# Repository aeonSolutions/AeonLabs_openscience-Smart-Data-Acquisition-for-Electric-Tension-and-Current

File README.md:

[PCB-Prototyping-Catalogue](https://github.com/aeonSolutions/PCB-Prototyping-Catalogue)  >>  [Laboratory Automation](https://github.com/aeonSolutions/PCB-Prototyping-Catalogue/tree/main/Laboratory%20Automation)  >>  Smart Data Acquisition for Electric Tension and Current

<br>

# Smart Data Acquisition for Electric Tension and Current
This is the repository for revision "11-2023" of the 16-bit Smart DAQ Device with a unique data fingerprint able to do experimental data upload to any data repository. This data acquisition device has oboard the INA237 IC and is suited for electric current measurements (amperage) and also electric tension (voltage) from an external power source. This IC from Texas Instruments is an ultra-precise digital power monitor with a 16-bit delta-sigma ADC specifically designed for current-sensing applications with common-mode voltage support from –0.3 V to +85 V. For more detailed information about this IC, see the datasheet [here](https://www.ti.com/product/INA237).

<br>

### Circuit Schematic
The circuit schematic for this smart DAQ can be found on the folder "circuit schematic" [here](https://github.com/aeonSolutions/AeonLabs_openscience-Smart-Data-Acquisition-for-Electric-Tension-and-Current/tree/main/Circuit%20Schematic). 

<br>

### Q & A
If you have a question and looking for an answer, there's a **Discussions** chat on the menu above.  Here's the [link](https://github.com/aeonSolutions/AeonLabs_openscience-Smart-Data-Acquisition-for-Electric-Tension-and-Current/discussions). You can post any question related to any of the Smart Data Acquisition devices and Experimental Setups.

<br>

### Known Experimental Tests
This smart data acquisition devices is compatible for the following laboratory experimental tests:

#### [NT Build 492](http://www.nordtest.info/wp/1999/11/21/concrete-mortar-and-cement-based-repair-materials-chloride-migration-coefficient-from-non-steady-state-migration-experiments-nt-build-492/): Concrete, mortar and cement-based repair materials: Chloride migration coefficient from non-steady-state migration experiments

See [here](https://github.com/aeonSolutions/Open-Scientific-Research/wiki/Rapid-Chloride-Migration-Test-(NT-Build-492)) a description of this experimental test procedure using the NT Build 492. 

<br>
  
#### other tests ...

<br>
<br>
 
## Compatibility

<p align="center">

</p>

<br>

## What one additionally needs
- [USB to UART/USB TTL firmware burner for 5V and 3.3V MCUs ](https://github.com/aeonSolutions/PCB-Prototyping-Catalogue/blob/main/DIY-Maker/README.md)
- [Upgradable ESP32 MCU](https://github.com/aeonSolutions/AeonLabs-Upgradable-MCU-ESP32)

<br />
<br />

**Get a Notification on every PCB update**

|  | You can fill in your [email here (Google form)](https://docs.google.com/forms/d/e/1FAIpQLScErMgQYRdA-umvCjvTPPrCO7Lg1QYowTxb7vfa8cTfrcPEAA/viewform?usp=pp_url) and I'll send a reminder when a new PCB prototype is made available here or a new revision for an existing PCB. Stay tuned! |
|-------------|------|

<br>
<br>

## Author

You can get in touch with me on my LinkedIn Profile:

#### Miguel Tomas

You can also follow my GitHub Profile to stay updated about my latest projects: 

**Hire me**

If you like my work here and are looking to design and deploy your own smart device you can hire me on:

- [Fiverr](https://www.fiverr.com/s/GjmPxe). The price starts at $25
- [Guru](https://www.guru.com/freelancers/miguel-tomas)
  
<br>

### Be supportive of my dedication and work towards technology education and buy me a cup of coffee
The PCB Desgin Files i provide here for anyone to use are free. If you like this Smart Device or use it, please consider buying me a cup of coffee, a slice of pizza or a book to help me study, eat and think new PCB design files.

<br />

### Make a donation on Paypal
Make a donation on paypal and get a TAX refund*.

<br>

### Support all these open hardware projects and become a patreon  
Liked any of my PCB KiCad Designs? Help and Support my open work to all by becomming a LDAD Patreon.
In return I will give a free PCB design in KiCad to all patreon supporters. To learn more go to patreon.com. Link below.

<br />
<br />

______________________________________________________________________________________________________________________________
### License

Before proceeding to download any of AeonLabs software solutions for open-source development and/or PCB hardware electronics development make sure you are choosing the right license for your project. See [AeonLabs Solutions for Open Hardware & Source Development](https://github.com/aeonSolutions/PCB-Prototyping-Catalogue/wiki/AeonLabs-Solutions-for-Open-Hardware-&-Source-Development) for more information.

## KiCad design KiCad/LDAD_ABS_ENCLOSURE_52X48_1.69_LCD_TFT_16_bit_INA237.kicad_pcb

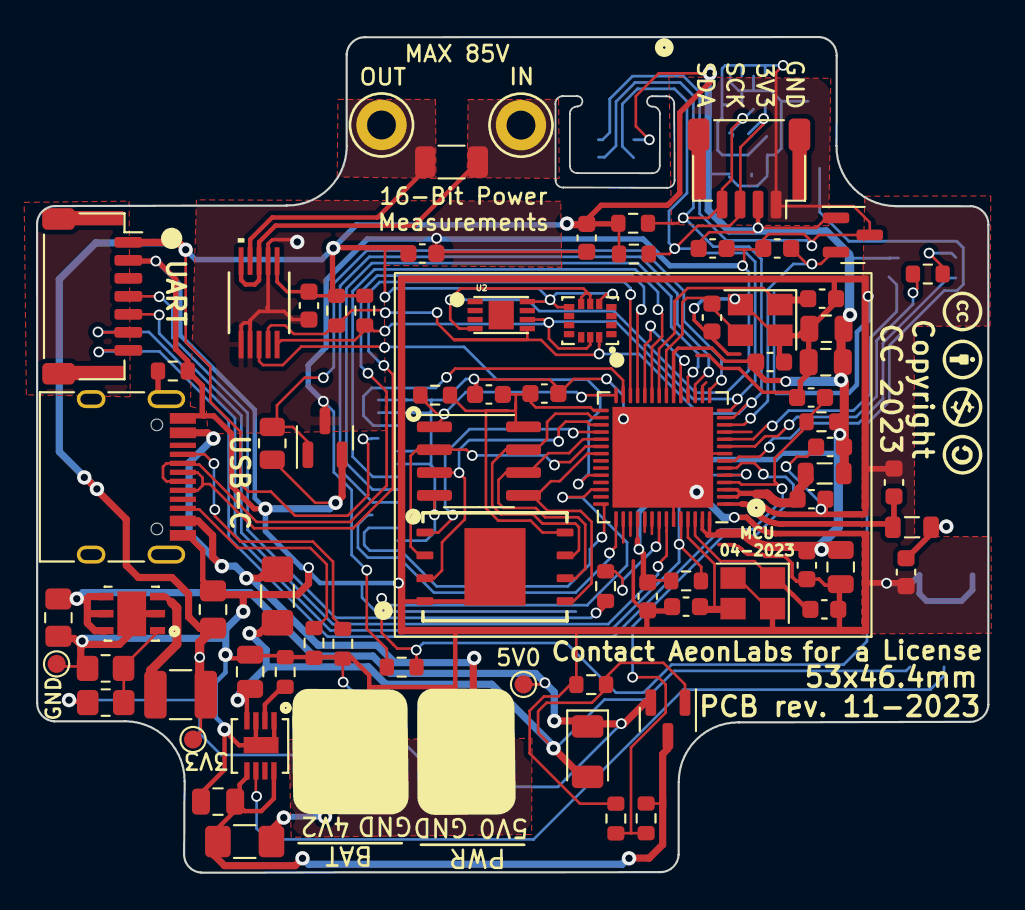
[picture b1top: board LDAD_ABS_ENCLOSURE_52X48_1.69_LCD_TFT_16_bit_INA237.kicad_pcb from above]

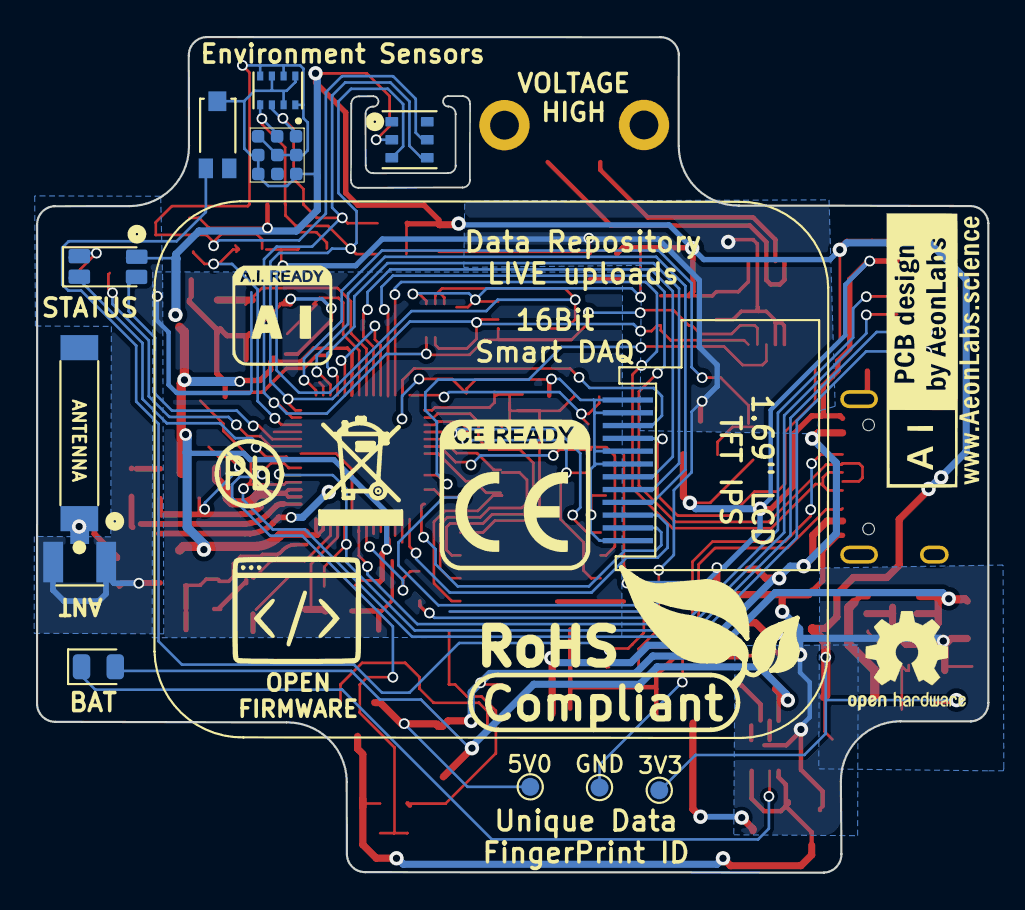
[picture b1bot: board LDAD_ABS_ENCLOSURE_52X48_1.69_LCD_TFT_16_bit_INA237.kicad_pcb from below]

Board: 2 copper layers, 52.9 x 46.4 mm, 90 parts (15 on the bottom side), 57 nets.

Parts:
ATH20_C2: 100nF; C_0603_1608Metric
ATSHA_C1: 100nF; C_0603_1608Metric
AUR1: AUR9718x_DFN_3x3mm_6_pin; AUR9718 ST1S09 SON95P300X300X100-7N
AUR_C1: 22uF; C_0805_2012Metric_Pad1.18x1.45mm_HandSolder
AUR_C2: 4.7uF; C_0805_2012Metric_Pad1.18x1.45mm_HandSolder
AUR_R1: 75k; R_0805_2012Metric_Pad1.20x1.40mm_HandSolder
AUR_R2: 24k; R_0805_2012Metric_Pad1.20x1.40mm_HandSolder
AUR_l1: 3.3uF; L_1210_3225Metric
BAT_FUSE1: Polyfuse; Fuse_1206_3216Metric_Pad1.42x1.75mm_HandSolder
BAT_SENSE_R1, BAT_SENSE_R2: 100k; R_0603_1608Metric
CN3065_C2: 4.7uF; C_0805_2012Metric
CN3065_R1: 1K8; R_0603_1608Metric
CN3065_STDBY_LED1: LED; LED_0805_2012Metric
CN3965_C1: 22uF; C_0805_2012Metric
DMP1045U_1: DMP1045U; SOT-23
DMP1045_R1: 10K; R_0603_1608Metric
DMP1045_SCHOT1: D_Schottky; D_1206_3216Metric
EPS1: ESP32-PSRAM_LY68L6400S; SOIC-8_3.9x4.9mm_P1.27mm
ER1: 1R; R_1206_3216Metric
ESP32S1: ESP32-S3; QFN-56-1EP_7x7mm_P0.4mm_EP5.6x5.6mm
ESP32_SHIELD1: RFShield_OnePiece; ESP32-S3 GND Shield
ESP_FLASH1: W25Q128JVS; WSON8 FLASH SPI SON127P800X600X80-9N
E_DTR_R1: 10k; R_0603_1608Metric
E_LNA_ANT1: AN9520; 2.4ghZ WIFI ANTENNA AN9520_ANT2-SMD-9.5X2.1X1.0MM
E_LNA_ANT2: U.FL-R-SMT(01); RF Antenna IPEX SMD PCB HRS_U.FL-R-SMT(01)
E_LNA_C1, E_LNA_C2: 2.7pF; C_0603_1608Metric
E_LNA_l1: 1.8nH 5%; L_0805_2012Metric
E_RTS_C1: 100nF; C_0603_1608Metric
E_RTS_R1: 10k; R_0603_1608Metric
E_SPI_C1: 1uF 10% 50V; C_0603_1608Metric
E_SPI_C2: 100nF 10% 16V; C_0603_1608Metric
E_UART_TX_1: 499R; R_0603_1608Metric
E_VDDA_C1: 100nF; C_0603_1608Metric
E_VDDA_C2: 1uF 10% 50V; C_0805_2012Metric
E_VDD_3_C1, E_VDD_3_C2: 10uF 20% 6.3V; C_0805_2012Metric
E_VDD_3_C3, E_VDD_3_C4: 100nF 10% 16V; C_0603_1608Metric
E_VDD_CPU_C1: 100nF 10% 16V; C_0603_1608Metric
E_VDD_L1: 12nH 5%; L_0805_2012Metric
E_VDD_RTC_C1: 100nF 10% 16V; C_0603_1608Metric
E_XTAL32_1: 32.768Mhz 22pF+-10PPM; Crystal_SMD_3225-4Pin_3.2x2.5mm
E_XTAL32_C1, E_XTAL32_C2, E_XTAL40_C1, E_XTAL40_C2: 22pF 5% 50V; C_0603_1608Metric
E_XTAL40_1: 40Mhz 22pF+-10PPM; Crystal_SMD_3225-4Pin_3.2x2.5mm
ExtSWBAT_PLUG2: Conn_01x03_Female; JST_SH_SM03B-SRSS-TB_1x03-1MP_P1.00mm_Horizontal
I2C_PLUG1: I2C6; JST_SH_SM04B-SRSS-TB_1x04-1MP_P1.00mm_Horizontal
I2C_SCL_R1, I2C_SDA_R1: 10k; R_0603_1608Metric
IC_ENS1: ENS160 Gas Semsor
IMR1, IMR2: 10K; R_0603_1608Metric
IMU1: LSM6DS3; LSM6DS3 Motion Sensor PQFN50P300X250X86-14N
INA4_C1: 100nF; C_0603_1608Metric
J1: TYPE-C-31-M-12; USB_C_Receptacle_HRO_TYPE-C-31-M-12
JICSP1: Conn_01x07_Socket; JST_SH_SM07B-SRSS-TB_1x07-1MP_P1.00mm_Horizontal
LCD1: Conn_01x12_Male; 1,69 inch LCD IPS TFT
LED1: LED_GBRC; LED_1206_3210_RGB_Metric
LR1: 330R; R_0603_1608Metric
MTRR1: 10k; R_0805_2012Metric
MTRT1: NPN; SOT-23
PSRAM_R1: 100K; R_0603_1608Metric
PWR_FUSE1: Polyfuse; Fuse_1206_3216Metric_Pad1.42x1.75mm_HandSolder
PWR_PLUG1: Screw_Terminal_01x02; JST_SH_SM02B-SRSS-TB_1x02-1MP_P1.00mm_Horizontal
Sign-PbFree: LOGO_PBFREE
Sign-RecycleBin: LOGO_RECYCLEBIN_1
Sign-RoHS: LOGO_ROHS_1
TMPR1: 10K; R_0603_1608Metric
TP1, TP1#2: VIN; TestPoint_Pad_D1.0mm
TP2, TP2#2: VOut; TestPoint_Pad_D1.0mm
TP3, TP3#2: GND; TestPoint_Pad_D1.0mm
U1: MCP1525-TT; SOT-23
U2: ATSHA204A-MAHDA-T; ATSHA204A-MAHDA-T UDFN-8
U3: Battery_charger_CN3065_QFN8; QFN8 3.1x2.9mm QFNn-8 3x3 SON80P400X400X100-9N
U4: AHT20; AHT20 HT Sensor PSON100P300X300X110-6N
U5: INA237AIDGSR; INA237
U6: TEMT6000; TEMT6000-SEN
U7: BMP280; XDCR_BMP280
USB_PLUG_R1, USB_PLUG_R3: 5k1; R_0603_1608Metric
USB_PLYG_R2: 150K; R_0603_1608Metric
VOLTAGE_REF_C1, VOLTAGE_REF_C2: 100nF; C_0603_1608Metric

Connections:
3V3: ATH20_C2.2, ATSHA_C1.2, AUR_C1.1, AUR_R1.1, AUR_l1.1, ESP32S1.20 (VDD3P3_RTC), ESP32S1.46 (VDD3P3_CPU), ESP32S1.55 (VDDA), ESP32S1.56 (VDDA), E_DTR_R1.1, E_RTS_R1.1, E_VDDA_C1.2, E_VDDA_C2.2, E_VDD_3_C1.1, E_VDD_3_C2.1, E_VDD_3_C3.1, E_VDD_CPU_C1.1, E_VDD_L1.1, E_VDD_RTC_C1.1, I2C_PLUG1.2, I2C_SCL_R1.1, I2C_SDA_R1.2, IC_ENS1.4 (VDD), IC_ENS1.5 (VDDIO), IC_ENS1.7 (CS), IMR1.1, IMR2.1, IMU1.5 (VDDIO), IMU1.8 (VDD), INA4_C1.2, JICSP1.1, LCD1.4, LED1.4 (K), TP2.1, TP2#2.1, U1.1 (Vin), U2.8 (VCC), U4.2 (VDD), U5.6 (VS), U6.COLLECTOR, U7.2 (CSB), U7.6 (VDDIO), U7.8 (VDD), VOLTAGE_REF_C1.2
BAT_SENSE_IO21: BAT_SENSE_R1.1, BAT_SENSE_R2.2, ESP32S1.6 (GPIO1/ADC1_CH0)
CHIP_EN: ESP32S1.4 (CHIP_PU/RESET), E_RTS_C1.2, E_RTS_R1.2, JICSP1.7
DAC_CALIBRATION: ESP32S1.19 (GPIO14/ADC2_CH3), ESP32S1.24 (GPIO18/ADC2_CH7/DAC_1)
ESP_GPIO0_BOOT-DTR: ESP32S1.5 (GPIO0/BOOT), ESP32S1.52 (GPIO46), E_DTR_R1.2, JICSP1.6
GND: AUR1.2 (GND), AUR1.7 (GND), AUR_C1.2, AUR_C2.2, AUR_R2.2, BAT_SENSE_R1.2, CN3065_C2.1, CN3065_R1.1, CN3965_C1.1, DMP1045_R1.2, EPS1.4 (VSS), ESP32S1.8 (GPIO3/ADC1_CH2), ESP32S1.51 (GPIO45), ESP32S1.57 (GND), ESP32_SHIELD1.1 (Shield), ESP_FLASH1.4 (GND), ESP_FLASH1.9 (GND), E_LNA_ANT2.1 (GND), E_LNA_ANT2.2 (GND), E_LNA_C1.2, E_LNA_C2.2, E_RTS_C1.1, E_SPI_C1.2, E_SPI_C2.2, E_VDDA_C1.1, E_VDDA_C2.1, E_VDD_3_C1.2, E_VDD_3_C2.2, E_VDD_3_C3.2, E_VDD_3_C4.2, E_VDD_CPU_C1.2, E_VDD_RTC_C1.2, E_XTAL32_1.2, E_XTAL32_1.4, E_XTAL32_C1.2, E_XTAL32_C2.2, E_XTAL40_1.2, E_XTAL40_1.4, E_XTAL40_C1.2, E_XTAL40_C2.2, ExtSWBAT_PLUG2.3, J1.B1, J1.B12, JICSP1.2, LCD1.1, LCD1.2, LCD1.5, LCD1.6, LCD1.12, MTRR1.1, MTRT1.2, PWR_PLUG1.1, TP3.1, TP3#2.1, U3.1 (V_Temp), U3.3 (GND), U3.9 (GND), USB_PLUG_R1.2, USB_PLUG_R3.2, USB_PLYG_R2.2
GNDD: ATH20_C2.1, ATSHA_C1.1, I2C_PLUG1.1, IC_ENS1.3 (MISO), IC_ENS1.8 (VSS), IC_ENS1.9 (VSS), IMU1.6 (GND), IMU1.7 (GND), INA4_C1.1, MTRT1.3, TMPR1.1, U1.3 (Vss), U2.4 (GND), U4.5 (GND), U5.1 (A1), U5.2 (A0), U5.7 (GND), U7.1 (GND), U7.5 (SDO), U7.7 (GND), VOLTAGE_REF_C1.1, VOLTAGE_REF_C2.1
GPIO8_I2C_SDA: ESP32S1.13 (GPIO8/ADC1_CH7), I2C_PLUG1.4, I2C_SDA_R1.1, IC_ENS1.1 (SDA), IMR1.2, IMU1.14 (SDA), U2.5 (SDA), U4.4 (SDA), U5.4 (SDA), U7.3 (SDI)
GPIO9_I2C_SCL: ESP32S1.14 (GPIO9/ADC1_CH8), I2C_PLUG1.3, I2C_SCL_R1.2, IC_ENS1.2 (SCL), IMR2.2, IMU1.13 (SCL), U2.6 (SCL), U4.3 (SCL), U5.5 (SCL), U7.4 (SCK)
INA237_ALRT_IO33: ESP32S1.38 (GPIO33), U5.3 (ALERT)
INA237_PROBE_+: ER1.2, U5.8 (VBUS), U5.10 (IN+)
INA237_PROBE_-: ER1.1, U5.9 (IN-)
LCD_CS_IO13: ESP32S1.18 (GPIO13/ADC2_CH2), LCD1.8
LCD_DC_IO17: ESP32S1.23 (GPIO17/ADC2_CH6/DAC_2), LCD1.7
LCD_I2C_SCL_IO12: ESP32S1.17 (GPIO12/ADC2_CH1), LCD1.9
LCD_I2C_SDA_IO38: ESP32S1.43 (GPIO38), LCD1.10
LCD_LED_IO21: ESP32S1.27 (GPIO21), LCD1.3
LCD_RST_IO37: ESP32S1.42 (GPIO37), LCD1.11
LED_B_IO05: ESP32S1.10 (GPIO5/ADC1_CH4), LED1.2 (BA)
LED_G_IO02: ESP32S1.7 (GPIO2/ADC1_CH1), LED1.1 (GA)
LED_R_IO04: ESP32S1.9 (GPIO4/ADC1_CH3), LR1.1
unnamed: AUR1.1 (FB), AUR_R1.2, AUR_R2.1
unnamed: AUR1.3 (SW), AUR_l1.2
unnamed: ESP32S1.21 (GPIO15/ADC2_CH4/XTAL_32K_P), E_XTAL32_1.3, E_XTAL32_C1.1
unnamed: ESP32S1.22 (GPIO16/ADC2_CH5/XTAL_32K_N), E_XTAL32_1.1, E_XTAL32_C2.1
unnamed: ESP32S1.1 (LNA_IN/RF), E_LNA_C2.1, E_LNA_l1.2
unnamed: ESP32S1.49 (U0TXD/PROG/GPIO43), E_UART_TX_1.2
unnamed: ESP32S1.2 (VDD3P3), ESP32S1.3 (VDD3P3), E_VDD_3_C4.1, E_VDD_L1.2
unnamed: ESP32S1.53 (XTAL_N), E_XTAL40_1.3, E_XTAL40_C2.1
unnamed: ESP32S1.54 (XTAL_P), E_XTAL40_1.1, E_XTAL40_C1.1
unnamed: E_LNA_ANT1.1, E_LNA_ANT2.3 (SIG), E_LNA_C1.1, E_LNA_l1.1
unnamed: J1.A5 (CC1), USB_PLUG_R3.1
unnamed: J1.B5 (CC2), USB_PLUG_R1.1
unnamed: J1.S1 (SHIELD), USB_PLYG_R2.1
unnamed: LED1.3 (RA), LR1.2
unnamed: CN3065_R1.2, U3.2 (I_SET)
PERIPHERALS_PWR_EN_IO10: ESP32S1.15 (GPIO10/ADC1_CH9), MTRR1.2, MTRT1.1
RXD0: ESP32S1.50 (U0RXD/PROG/GPIO44), JICSP1.5
SPICLK: EPS1.6 (SCLK), ESP32S1.33 (SPICLK/GPIO30), ESP_FLASH1.6 (CLK)
SPICS0: ESP32S1.32 (SPICS0/GPIO29), ESP_FLASH1.1 (~CS)
SPICS1: EPS1.1 (~CE), ESP32S1.28 (SPI_CS1/GPIO26), PSRAM_R1.1
SPID: EPS1.5 (SiO0), ESP32S1.35 (SPID/GPIO32), ESP_FLASH1.5 (DI(IO0))
SPIHD: EPS1.7 (SIO3), ESP32S1.30 (SPIHD/GPIO27), ESP_FLASH1.7 (IO3)
SPIQ: EPS1.2 (SIO1), ESP32S1.34 (SPIQ/GPIO31), ESP_FLASH1.2 (DO(IO1))
SPIWP: EPS1.3 (SIO2), ESP32S1.31 (SPIWP/GPIO28), ESP_FLASH1.3 (IO2)
STDBY_LED_G: CN3065_STDBY_LED1.1 (K), U3.6 (LED_DONE)
TEMT6000_IO35: ESP32S1.40 (GPIO35), TMPR1.2, U6.EMITTER
TXD0: E_UART_TX_1.1, JICSP1.4
USB_5V0: CN3065_STDBY_LED1.2 (A), CN3965_C1.2, DMP1045U_1.1, DMP1045_R1.1, DMP1045_SCHOT1.2 (A), PWR_FUSE1.1, U3.4 (VIN)
USB_5V0F: J1.A4, J1.A9, PWR_FUSE1.2, PWR_PLUG1.2
USB_D+: ESP32S1.26 (GPIO20/USB_D+/ADC2_CH9), J1.A6 (DP1), J1.B6 (DP2)
USB_D-: ESP32S1.25 (GPIO19/USB_D-/ADC2_CH8), J1.A7 (DN1), J1.B7 (DN2)
VDD_SPI: EPS1.8 (VCC), ESP32S1.29 (VDD_SPI), ESP_FLASH1.8 (VCC), E_SPI_C1.1, E_SPI_C2.1, PSRAM_R1.2
VIN: AUR1.4 (VIN_SW), AUR1.5 (VIN_A), AUR1.6 (EN), AUR_C2.1, DMP1045U_1.2, DMP1045_SCHOT1.1 (K), TP1.1, TP1#2.1
VIN_BAT: BAT_FUSE1.1, BAT_SENSE_R2.1, CN3065_C2.2, DMP1045U_1.3, U3.5 (BAT+), U3.8 (FB)
VIN_BATF: BAT_FUSE1.2, ExtSWBAT_PLUG2.1
VOLTAGE_REF_IO07: ESP32S1.12 (GPIO7/ADC1_CH6), U1.2 (Vout), VOLTAGE_REF_C2.2
